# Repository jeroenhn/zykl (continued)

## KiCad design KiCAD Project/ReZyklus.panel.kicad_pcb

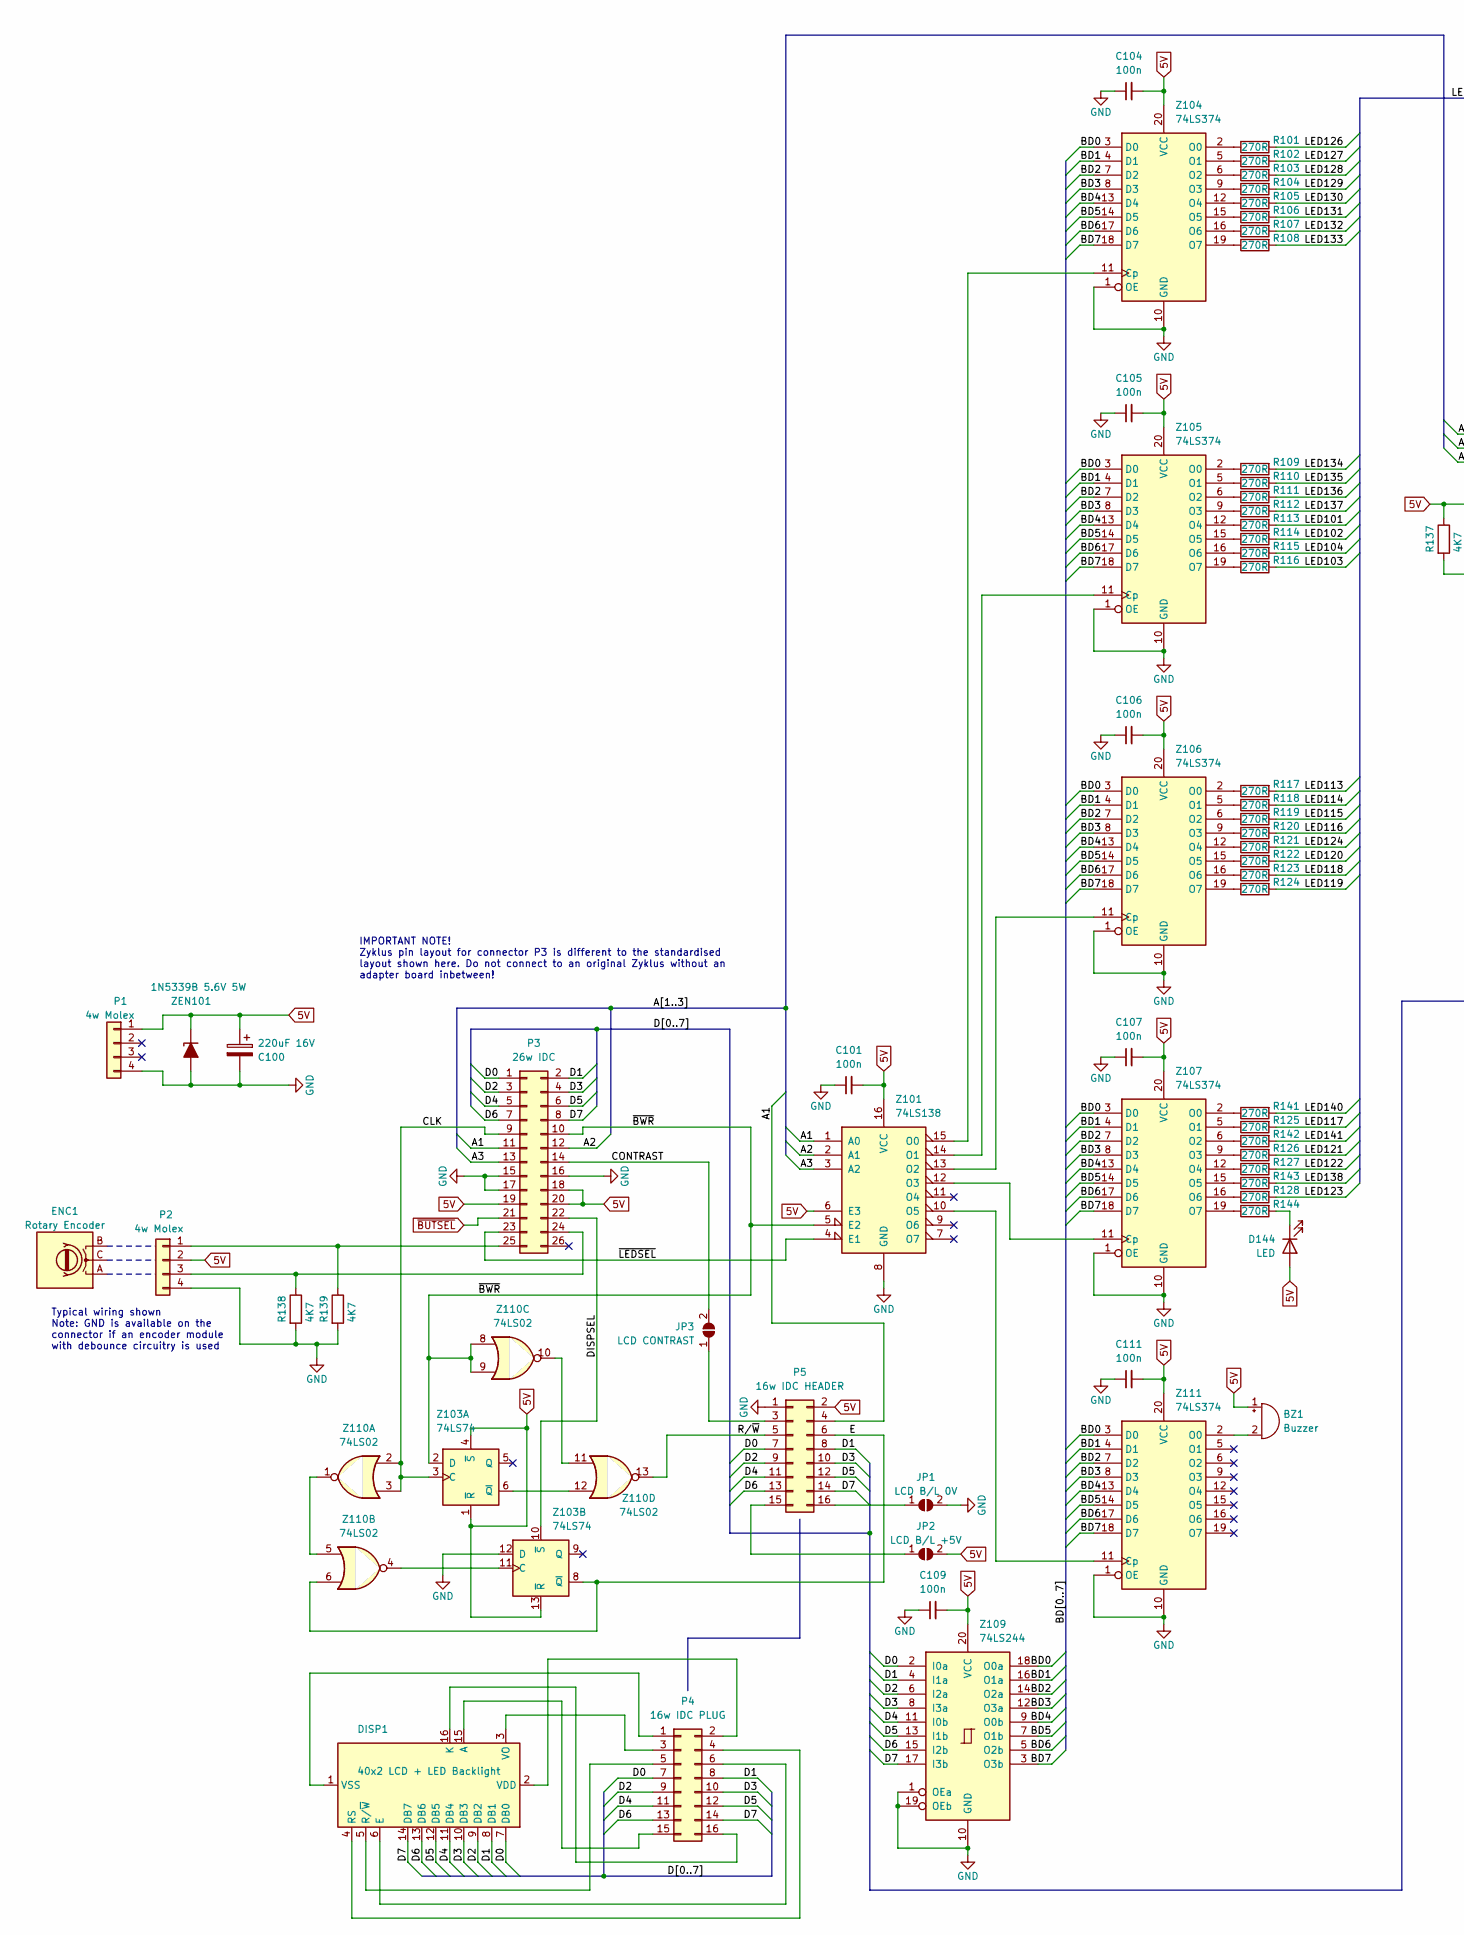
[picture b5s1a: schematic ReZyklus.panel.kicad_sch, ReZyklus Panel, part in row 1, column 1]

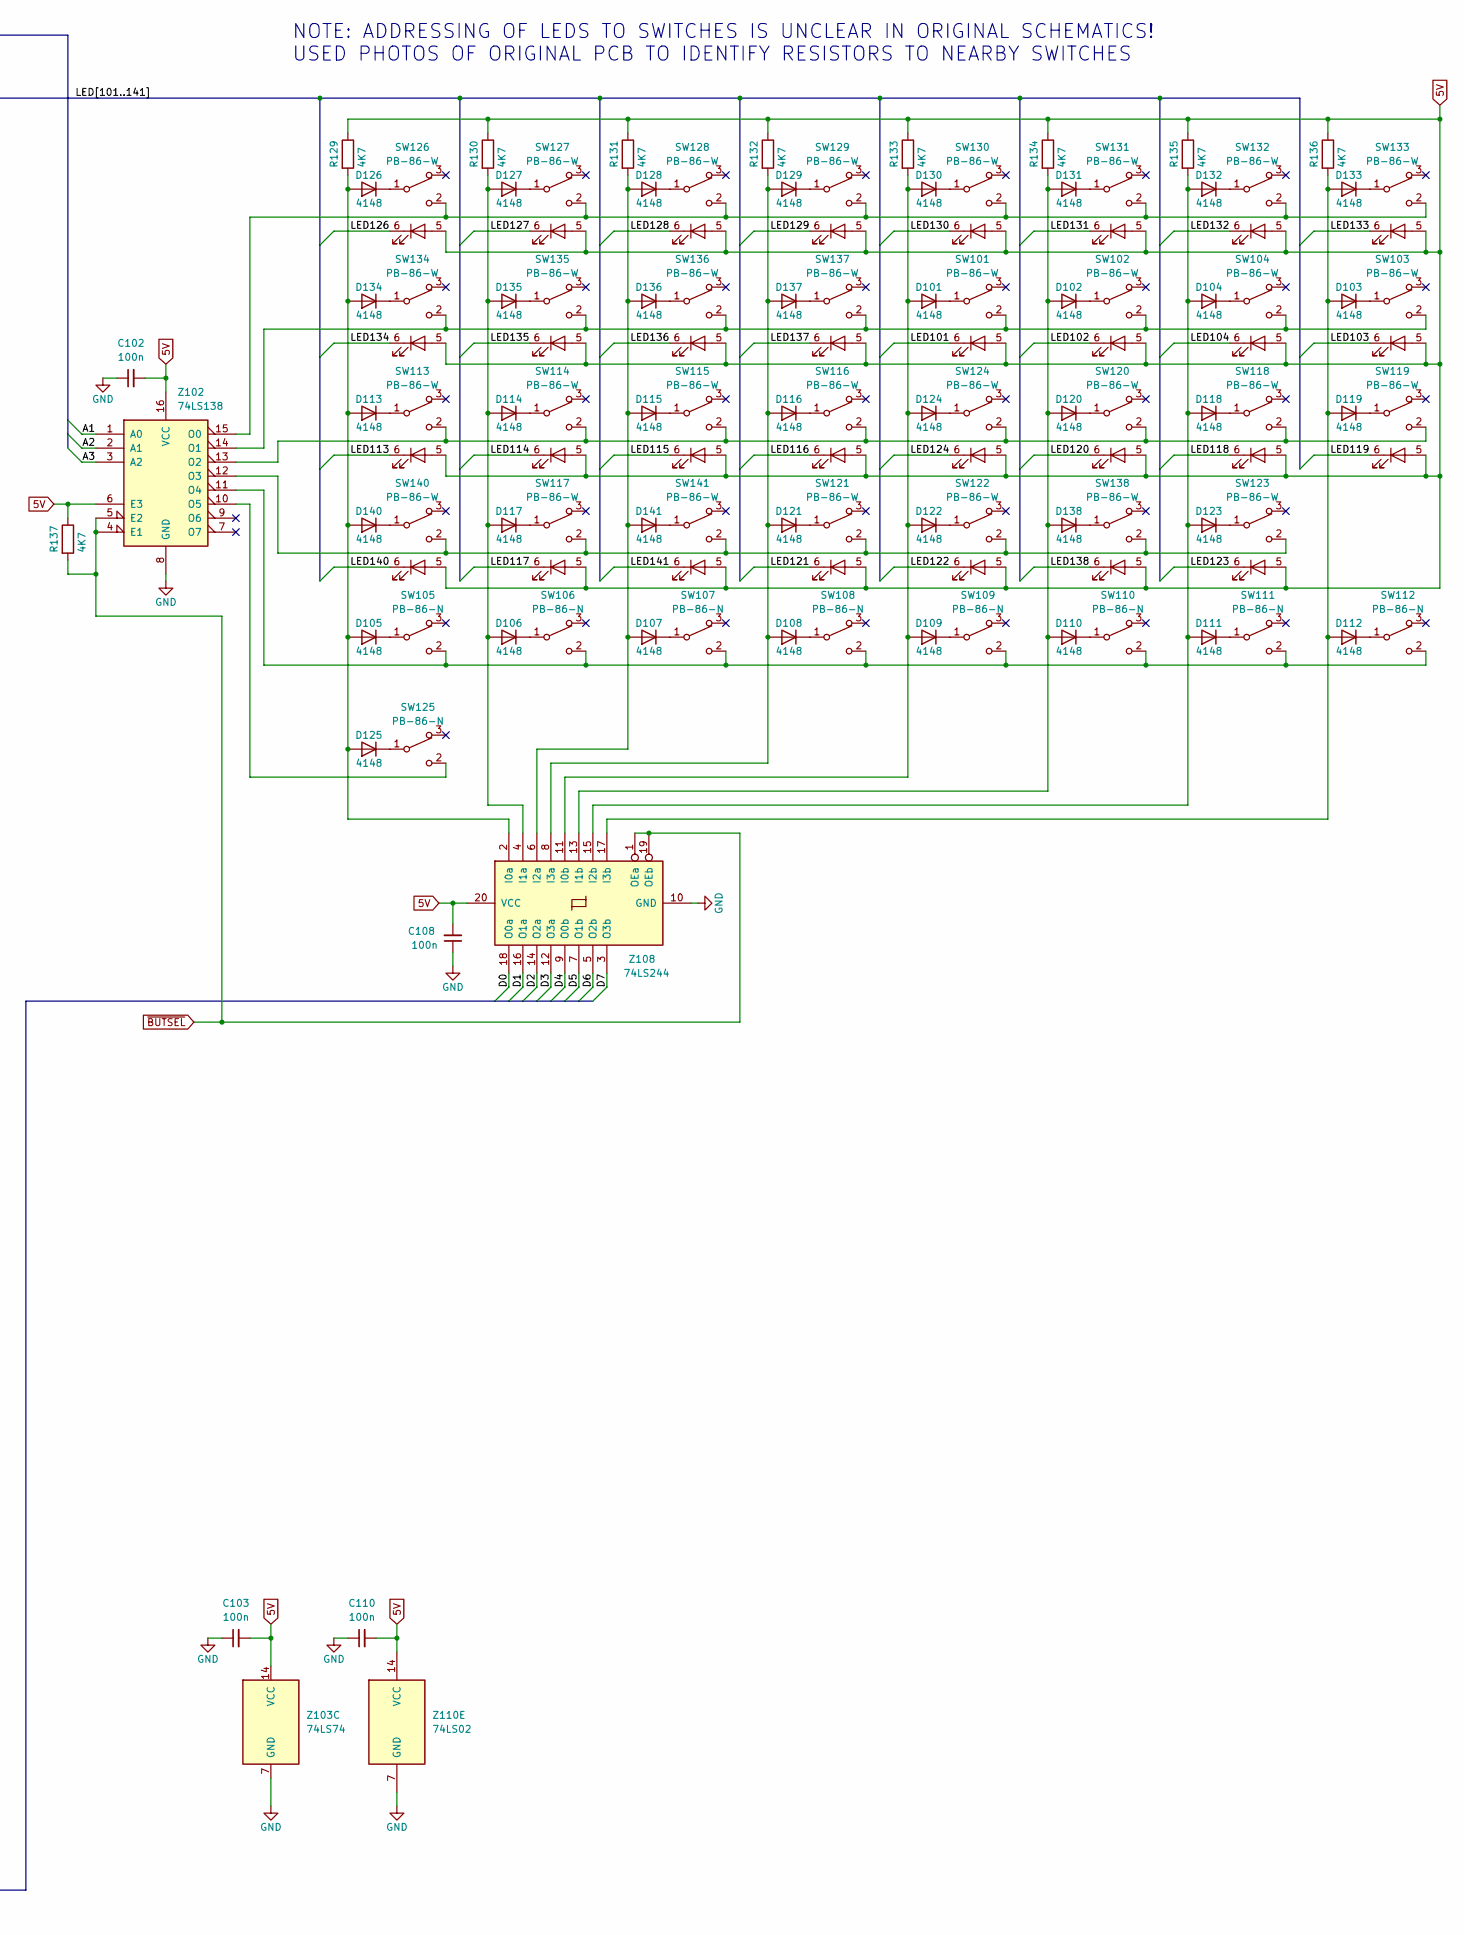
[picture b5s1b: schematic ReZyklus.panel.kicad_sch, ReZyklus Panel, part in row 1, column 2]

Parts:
BZ1: Buzzer; Buzzer_12x9.5RM7.6
C100: 220uF 16V; CP_Radial_D8.0mm_P3.50mm
C101, C102, C103, C104, C105, C106, C107, C108, C109, C110, C111: 100n; C_Rect_L7.0mm_W2.5mm_P5.00mm
D101, D102, D103, D104, D105, D106, D107, D108, D109, D110, D111, D112, D113, D114, D115, D116, D117, D118, D119, D120, D121, D122, D123, D124, D125, D126, D127, D128, D129, D130, D131, D132, D133, D134, D135, D136, D137, D138, D140, D141: 4148; D_DO-35_SOD27_P7.62mm_Horizontal
D144: LED; LED_D5.0mm
DISP1: 40x2 LCD + LED Backlight
ENC1: Rotary Encoder; RotaryEncoder_Alps_EC12E_Vertical_H20mm
JP1: LCD B/L 0V; SolderJumper-2_P1.3mm_Open_RoundedPad1.0x1.5mm
JP2: LCD B/L +5V; SolderJumper-2_P1.3mm_Open_RoundedPad1.0x1.5mm
JP3: LCD CONTRAST; SolderJumper-2_P1.3mm_Open_RoundedPad1.0x1.5mm
P1: 4w Molex; Molex_KK-396_5273-04A_1x04_P3.96mm_Vertical
P2: 4w Molex; JST_XA_B04B-XASK-1_1x04_P2.50mm_Vertical
P3: 26w IDC; IDC-Header_2x13_P2.54mm_Latch_Vertical
P4: 16w IDC PLUG
P5: 16w IDC HEADER; IDC-Header_2x08_P2.54mm_Vertical
R101, R102, R103, R104, R105, R106, R107, R108, R109, R110, R111, R112, R113, R114, R115, R116, R117, R118, R119, R120, R121, R122, R123, R124, R125, R126, R127, R128, R141, R142, R143, R144: 270R; R_Axial_DIN0207_L6.3mm_D2.5mm_P10.16mm_Horizontal
R129, R130, R131, R132, R133, R134, R135, R136, R137, R138, R139: 4K7; R_Axial_DIN0207_L6.3mm_D2.5mm_P10.16mm_Horizontal
SW101, SW102, SW103, SW104, SW113, SW114, SW115, SW116, SW117, SW118, SW119, SW120, SW121, SW122, SW123, SW124, SW126, SW127, SW128, SW129, SW130, SW131, SW132, SW133, SW134, SW135, SW136, SW137, SW138, SW140, SW141: PB-86-W
SW105, SW106, SW107, SW108, SW109, SW110, SW111, SW112, SW125: PB-86-N
Z101, Z102: 74LS138; DIP-16_W7.62mm_Socket_LongPads
Z103: 74LS74; DIP-14_W7.62mm_Socket_LongPads
Z104, Z105, Z106, Z107, Z111: 74LS374; DIP-20_W7.62mm_Socket_LongPads
Z108, Z109: 74LS244; DIP-20_W7.62mm_Socket_LongPads
Z110: 74LS02; DIP-14_W7.62mm_Socket_LongPads
ZEN101: 1N5339B 5.6V 5W; D_DO-27_P12.70mm_Horizontal

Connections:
5V: BZ1.1 (-), C100.1, C101.2, C102.2, C103.2, C104.2, C105.2, C106.2, C107.2, C108.2, C109.2, C110.2, C111.2, D144.2 (A), JP2.2 (B), P1.1, P2.2, P3.18, P3.19, P3.20, P5.2, R129.1, R130.1, R131.1, R132.1, R133.1, R134.1, R135.1, R136.1, R137.1, SW101.5, SW102.5, SW103.5, SW104.5, SW113.5, SW114.5, SW115.5, SW116.5, SW117.5, SW118.5, SW119.5, SW120.5, SW121.5, SW122.5, SW123.5, SW124.5, SW126.5, SW127.5, SW128.5, SW129.5, SW130.5, SW131.5, SW132.5, SW133.5, SW134.5, SW135.5, SW136.5, SW137.5, SW138.5, SW140.5, SW141.5, Z101.6 (E3), Z101.16 (VCC), Z102.6 (E3), Z102.16 (VCC), Z103.1 (~R), Z103.4 (~S), Z103.13 (~R), Z103.14 (VCC), Z104.20 (VCC), Z105.20 (VCC), Z106.20 (VCC), Z107.20 (VCC), Z108.20 (VCC), Z109.20 (VCC), Z110.14 (VCC), Z111.20 (VCC), ZEN101.1 (K)
/A1: P3.11, P5.4, Z101.1 (A0), Z102.1 (A0)
/A2: P3.12, Z101.2 (A1), Z102.2 (A1)
/A3: P3.13, Z101.3 (A2), Z102.3 (A2)
/BD0: Z104.3 (D0), Z105.3 (D0), Z106.3 (D0), Z107.3 (D0), Z109.18 (O0a), Z111.3 (D0)
/BD1: Z104.4 (D1), Z105.4 (D1), Z106.4 (D1), Z107.4 (D1), Z109.16 (O1a), Z111.4 (D1)
/BD2: Z104.7 (D2), Z105.7 (D2), Z106.7 (D2), Z107.7 (D2), Z109.14 (O2a), Z111.7 (D2)
/BD3: Z104.8 (D3), Z105.8 (D3), Z106.8 (D3), Z107.8 (D3), Z109.12 (O3a), Z111.8 (D3)
/BD4: Z104.13 (D4), Z105.13 (D4), Z106.13 (D4), Z107.13 (D4), Z109.9 (O0b), Z111.13 (D4)
/BD5: Z104.14 (D5), Z105.14 (D5), Z106.14 (D5), Z107.14 (D5), Z109.7 (O1b), Z111.14 (D5)
/BD6: Z104.17 (D6), Z105.17 (D6), Z106.17 (D6), Z107.17 (D6), Z109.5 (O2b), Z111.17 (D6)
/BD7: Z104.18 (D7), Z105.18 (D7), Z106.18 (D7), Z107.18 (D7), Z109.3 (O3b), Z111.18 (D7)
/CLK: P3.9, Z103.3 (C), Z110.2, Z110.3
/CONTRAST: JP3.2 (B), P3.14
/D0: DISP1.7 (DB0), P3.1, P4.7, P5.7, Z108.18 (O0a), Z109.2 (I0a)
/D1: DISP1.8 (DB1), P3.2, P4.8, P5.8, Z108.16 (O1a), Z109.4 (I1a)
/D2: DISP1.9 (DB2), P3.3, P4.9, P5.9, Z108.14 (O2a), Z109.6 (I2a)
/D3: DISP1.10 (DB3), P3.4, P4.10, P5.10, Z108.12 (O3a), Z109.8 (I3a)
/D4: DISP1.11 (DB4), P3.5, P4.11, P5.11, Z108.9 (O0b), Z109.11 (I0b)
/D5: DISP1.12 (DB5), P3.6, P4.12, P5.12, Z108.7 (O1b), Z109.13 (I1b)
/D6: DISP1.13 (DB6), P3.7, P4.13, P5.13, Z108.5 (O2b), Z109.15 (I2b)
/D7: DISP1.14 (DB7), P3.8, P4.14, P5.14, Z108.3 (O3b), Z109.17 (I3b)
/DISPSEL: P3.22, Z103.10 (~S)
/E: P5.6, Z103.8 (~Q), Z110.6
/LED101: R113.2, SW101.6
/LED102: R114.2, SW102.6
/LED103: R116.2, SW103.6
/LED104: R115.2, SW104.6
/LED113: R117.2, SW113.6
/LED114: R118.2, SW114.6
/LED115: R119.2, SW115.6
/LED116: R120.2, SW116.6
/LED117: R125.2, SW117.6
/LED118: R123.2, SW118.6
/LED119: R124.2, SW119.6
/LED120: R122.2, SW120.6
/LED121: R126.2, SW121.6
/LED122: R127.2, SW122.6
/LED123: R128.2, SW123.6
/LED124: R121.2, SW124.6
/LED126: R101.2, SW126.6
/LED127: R102.2, SW127.6
/LED128: R103.2, SW128.6
/LED129: R104.2, SW129.6
/LED130: R105.2, SW130.6
/LED131: R106.2, SW131.6
/LED132: R107.2, SW132.6
/LED133: R108.2, SW133.6
/LED134: R109.2, SW134.6
/LED135: R110.2, SW135.6
/LED136: R111.2, SW136.6
/LED137: R112.2, SW137.6
/LED138: R143.2, SW138.6
/LED140: R141.2, SW140.6
/LED141: R142.2, SW141.6
/R/~W: P5.5, Z110.13
/~BWR: P3.10, Z101.5 (E2), Z103.2 (D), Z110.8, Z110.9
/~LEDSEL: P3.23, Z101.4 (E1)
GND: C100.2, C101.1, C102.1, C103.1, C104.1, C105.1, C106.1, C107.1, C108.1, C109.1, C110.1, C111.1, JP1.2 (B), P1.4, P2.4, P3.15, P3.16, P3.17, P5.1, R138.2, R139.2, Z101.8 (GND), Z102.8 (GND), Z103.7 (GND), Z103.12 (D), Z104.1 (OE), Z104.10 (GND), Z105.1 (OE), Z105.10 (GND), Z106.1 (OE), Z106.10 (GND), Z107.1 (OE), Z107.10 (GND), Z108.10 (GND), Z109.1 (OEa), Z109.10 (GND), Z109.19 (OEb), Z110.7 (GND), Z111.1 (OE), Z111.10 (GND), ZEN101.2 (A)
unnamed: BZ1.2 (+), Z111.2 (O0)
unnamed: D101.2 (A), D109.2 (A), D122.2 (A), D124.2 (A), D130.2 (A), R133.2, Z108.11 (I0b)
unnamed: D101.1 (K), SW101.1
unnamed: D102.2 (A), D110.2 (A), D120.2 (A), D131.2 (A), D138.2 (A), R134.2, Z108.13 (I1b)
unnamed: D102.1 (K), SW102.1
unnamed: D103.2 (A), D112.2 (A), D119.2 (A), D133.2 (A), R136.2, Z108.17 (I3b)
unnamed: D103.1 (K), SW103.1
unnamed: D104.2 (A), D111.2 (A), D118.2 (A), D123.2 (A), D132.2 (A), R135.2, Z108.15 (I2b)
unnamed: D104.1 (K), SW104.1
unnamed: D105.2 (A), D113.2 (A), D125.2 (A), D126.2 (A), D134.2 (A), D140.2 (A), R129.2, Z108.2 (I0a)
unnamed: D105.1 (K), SW105.1
unnamed: D106.2 (A), D114.2 (A), D117.2 (A), D127.2 (A), D135.2 (A), R130.2, Z108.4 (I1a)
unnamed: D106.1 (K), SW106.1
unnamed: D107.2 (A), D115.2 (A), D128.2 (A), D136.2 (A), D141.2 (A), R131.2, Z108.6 (I2a)
unnamed: D107.1 (K), SW107.1
unnamed: D108.2 (A), D116.2 (A), D121.2 (A), D129.2 (A), D137.2 (A), R132.2, Z108.8 (I3a)
unnamed: D108.1 (K), SW108.1
unnamed: D109.1 (K), SW109.1
unnamed: D110.1 (K), SW110.1
unnamed: D111.1 (K), SW111.1
unnamed: D112.1 (K), SW112.1
unnamed: D113.1 (K), SW113.1
unnamed: D114.1 (K), SW114.1
unnamed: D115.1 (K), SW115.1
unnamed: D116.1 (K), SW116.1
unnamed: D117.1 (K), SW117.1
unnamed: D118.1 (K), SW118.1
unnamed: D119.1 (K), SW119.1
unnamed: D120.1 (K), SW120.1
unnamed: D121.1 (K), SW121.1
unnamed: D122.1 (K), SW122.1
unnamed: D123.1 (K), SW123.1
unnamed: D124.1 (K), SW124.1
unnamed: D125.1 (K), SW125.1
unnamed: D126.1 (K), SW126.1
unnamed: D127.1 (K), SW127.1
unnamed: D128.1 (K), SW128.1
unnamed: D129.1 (K), SW129.1
unnamed: D130.1 (K), SW130.1
unnamed: D131.1 (K), SW131.1
unnamed: D132.1 (K), SW132.1
unnamed: D133.1 (K), SW133.1
unnamed: D134.1 (K), SW134.1
unnamed: D135.1 (K), SW135.1
unnamed: D136.1 (K), SW136.1
unnamed: D137.1 (K), SW137.1
unnamed: D138.1 (K), SW138.1
unnamed: D140.1 (K), SW140.1
unnamed: D141.1 (K), SW141.1
unnamed: D144.1 (K), R144.2
unnamed: DISP1.1 (VSS), P4.1
unnamed: DISP1.2 (VDD), P4.2
unnamed: DISP1.3 (VO), P4.3
unnamed: DISP1.4 (RS), P4.4
unnamed: DISP1.5 (R/~W), P4.5
unnamed: DISP1.6 (E), P4.6
unnamed: DISP1.15 (A), P4.15
unnamed: DISP1.16 (K), P4.16
unnamed: JP1.1 (A), P5.16
unnamed: JP2.1 (A), P5.15
unnamed: JP3.1 (A), P5.3
unnamed: P2.1, P3.25, R139.1
unnamed: P2.3, P3.24, R138.1
unnamed: Z101.15 (O0), Z104.11 (Cp)
unnamed: Z101.14 (O1), Z105.11 (Cp)
unnamed: Z101.13 (O2), Z106.11 (Cp)
unnamed: Z101.12 (O3), Z107.11 (Cp)
unnamed: Z101.10 (O5), Z111.11 (Cp)
unnamed: SW126.2, SW127.2, SW128.2, SW129.2, SW130.2, SW131.2, SW132.2, SW133.2, Z102.15 (O0)
unnamed: SW101.2, SW102.2, SW103.2, SW104.2, SW134.2, SW135.2, SW136.2, SW137.2, Z102.14 (O1)
unnamed: SW113.2, SW114.2, SW115.2, SW116.2, SW118.2, SW119.2, SW120.2, SW124.2, Z102.13 (O2)
unnamed: SW117.2, SW121.2, SW122.2, SW123.2, SW138.2, SW140.2, SW141.2, Z102.12 (O3)
unnamed: SW105.2, SW106.2, SW107.2, SW108.2, SW109.2, SW110.2, SW111.2, SW112.2, Z102.11 (O4)
unnamed: SW125.2, Z102.10 (O5)
unnamed: Z103.6 (~Q), Z110.12
unnamed: Z103.11 (C), Z110.4
unnamed: R101.1, Z104.2 (O0)
unnamed: R102.1, Z104.5 (O1)
unnamed: R103.1, Z104.6 (O2)
unnamed: R104.1, Z104.9 (O3)
unnamed: R105.1, Z104.12 (O4)
unnamed: R106.1, Z104.15 (O5)
unnamed: R107.1, Z104.16 (O6)
unnamed: R108.1, Z104.19 (O7)
unnamed: R109.1, Z105.2 (O0)
unnamed: R110.1, Z105.5 (O1)
unnamed: R111.1, Z105.6 (O2)
unnamed: R112.1, Z105.9 (O3)
unnamed: R113.1, Z105.12 (O4)
unnamed: R114.1, Z105.15 (O5)
unnamed: R115.1, Z105.16 (O6)
unnamed: R116.1, Z105.19 (O7)
unnamed: R117.1, Z106.2 (O0)
unnamed: R118.1, Z106.5 (O1)
unnamed: R119.1, Z106.6 (O2)
unnamed: R120.1, Z106.9 (O3)
unnamed: R121.1, Z106.12 (O4)
unnamed: R122.1, Z106.15 (O5)
unnamed: R123.1, Z106.16 (O6)
unnamed: R124.1, Z106.19 (O7)
unnamed: R141.1, Z107.2 (O0)
unnamed: R125.1, Z107.5 (O1)
unnamed: R142.1, Z107.6 (O2)
unnamed: R126.1, Z107.9 (O3)
unnamed: R127.1, Z107.12 (O4)
unnamed: R143.1, Z107.15 (O5)
unnamed: R128.1, Z107.16 (O6)
unnamed: R144.1, Z107.19 (O7)
unnamed: Z110.1, Z110.5
unnamed: Z110.10, Z110.11
~BUTSEL: P3.21, R137.2, Z102.4 (E1), Z102.5 (E2), Z108.1 (OEa), Z108.19 (OEb)

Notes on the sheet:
Typical wiring shown Note: GND is available on the connector if an encoder module with debounce circuitry is used
IMPORTANT NOTE! Zyklus pin layout for connector P3 is different to the standardised layout shown here. Do not connect to an original Zyklus without an adapter board inbetween!
NOTE: ADDRESSING OF LEDS TO SWITCHES IS UNCLEAR IN ORIGINAL SCHEMATICS! USED PHOTOS OF ORIGINAL PCB TO IDENTIFY RESISTORS TO NEARBY SWITCHES

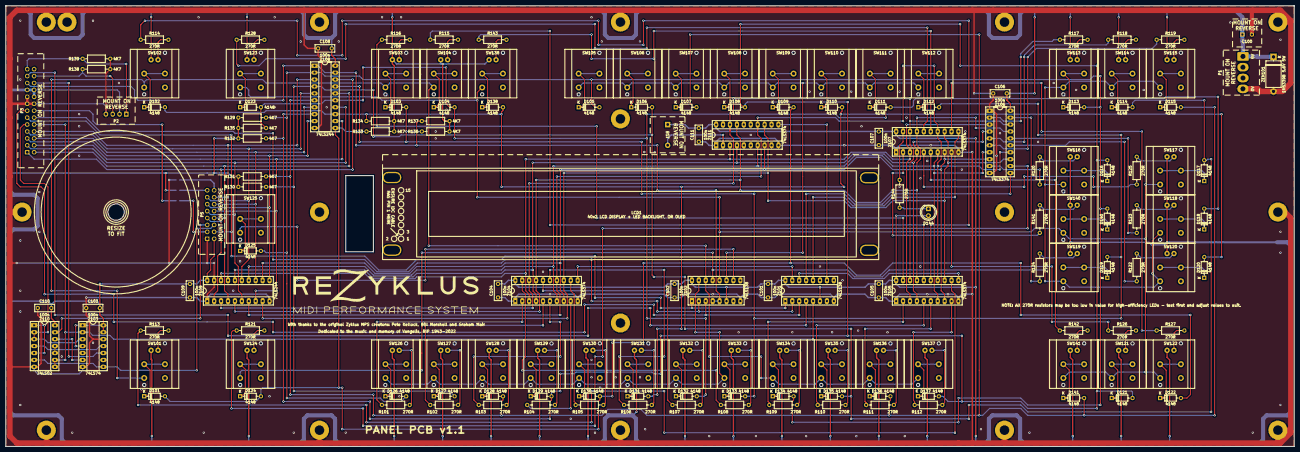
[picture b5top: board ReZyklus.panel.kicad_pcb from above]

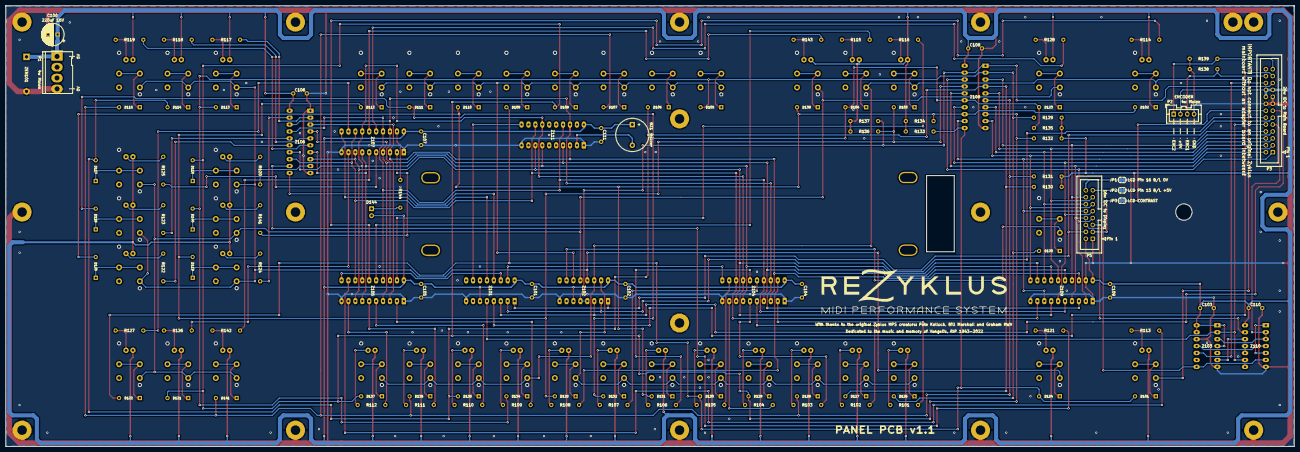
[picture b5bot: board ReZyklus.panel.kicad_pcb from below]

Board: 2 copper layers, 472.7 x 161.7 mm, 157 parts (9 on the bottom side), 162 nets.

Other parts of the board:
LCD1: 40x2 LCD DISPLAY + LED BACKLIGHT, OR OLED; 40x2_LCD_Type1

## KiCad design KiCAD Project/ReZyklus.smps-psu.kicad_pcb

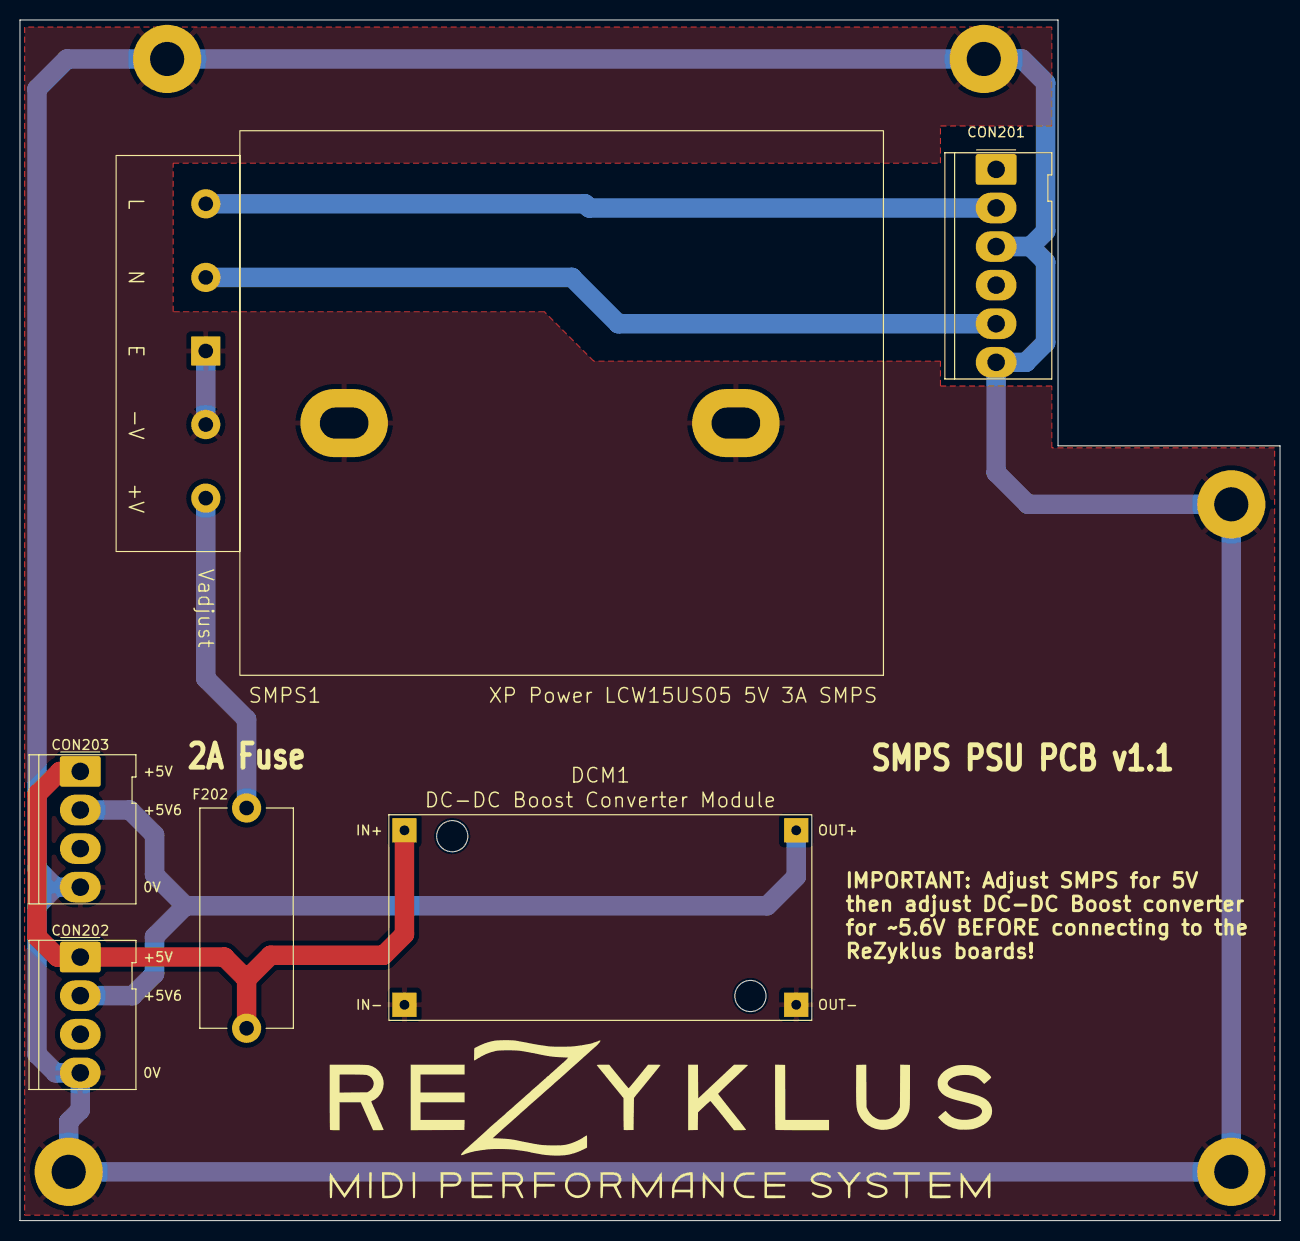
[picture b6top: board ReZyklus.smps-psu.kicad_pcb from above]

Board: 2 copper layers, 129.3 x 123.2 mm, 11 parts (0 on the bottom side), 6 nets.

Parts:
CON201: 5W HDR; Molex_KK-396_5273-06A_1x06_P3.96mm_Vertical
CON202, CON203: 4w Molex; Molex_KK-396_5273-04A_1x04_P3.96mm_Vertical
DCM1: DC-DC Boost Converter Module; LM2596_DC-DC_Converter_Module
F202: 2A; Fuseholder_Cylinder-5x20mm_Stelvio-Kontek_PTF78_Horizontal_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
REF1, REF2, REF3, REF4, REF5: MountingHole_3.5mm_Pad
SMPS1: XP Power LCW15US05 5V 3A SMPS; XPPower-LCW15US05_5V_3A_SMPS

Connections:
/+5.6V: CON202.2, CON203.2, DCM1.3 (OUT+)
/+5V: CON202.1, CON203.1, DCM1.1 (IN+), F202.2
/AC-L: CON201.2, SMPS1.1 (AC(L))
/AC-N: CON201.5, SMPS1.2 (AC(N))
GND: CON201.3, CON201.6, CON202.4, CON203.4, DCM1.2 (IN-), DCM1.4 (OUT-), SMPS1.3 (EARTH), SMPS1.4 (-Vout)
unnamed: F202.1, SMPS1.5 (+Vout)

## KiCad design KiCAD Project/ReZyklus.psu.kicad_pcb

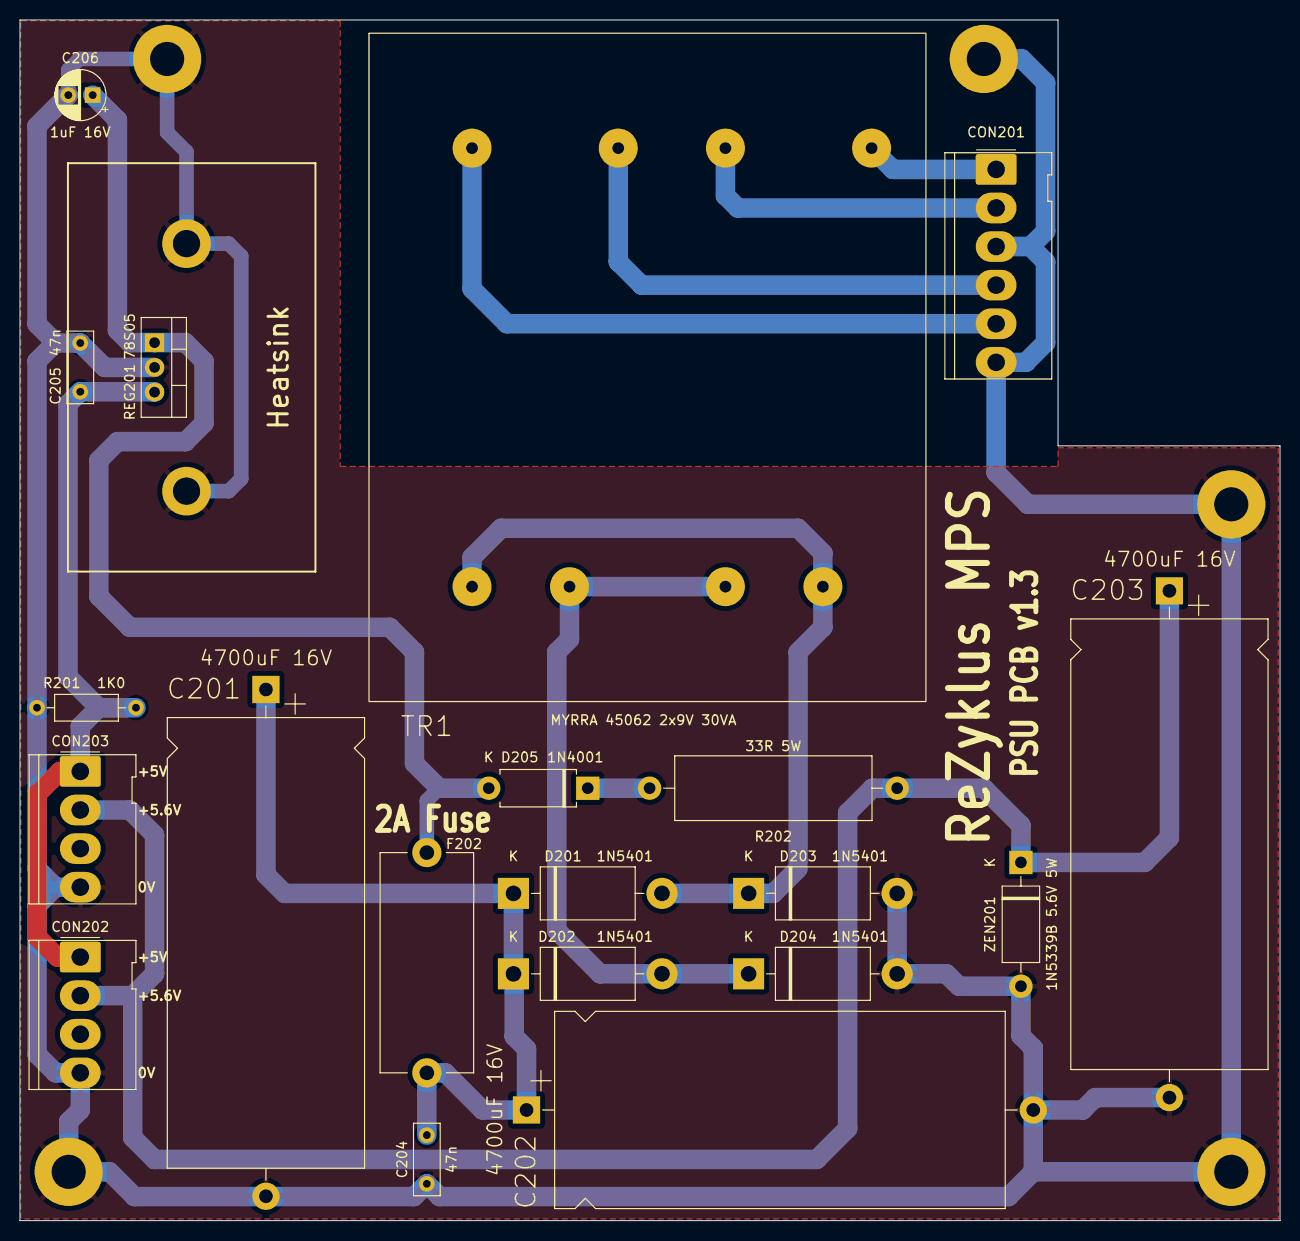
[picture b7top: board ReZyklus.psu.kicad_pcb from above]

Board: 2 copper layers, 129.3 x 123.2 mm, 25 parts (0 on the bottom side), 12 nets.

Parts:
C201, C202, C203: 4700uF 16V; CP_Axial_L46.0mm_D20.0mm_P52.00mm_Horizontal
C204, C205: 47n; C_Rect_L7.2mm_W2.5mm_P5.00mm_FKS2_FKP2_MKS2_MKP2
C206: 1uF 16V; CP_Radial_D5.0mm_P2.50mm
CON201: 5W HDR; Molex_KK-396_5273-06A_1x06_P3.96mm_Vertical
CON202, CON203: 4w Molex; Molex_KK-396_5273-04A_1x04_P3.96mm_Vertical
D201, D202, D203, D204: 1N5401; D_DO-201AD_P15.24mm_Horizontal
D205: 1N4001; D_DO-15_P10.16mm_Horizontal
F202: 2A; Fuseholder_Cylinder-5x20mm_Stelvio-Kontek_PTF78_Horizontal_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
R201: 1K0; R_Axial_DIN0207_L6.3mm_D2.5mm_P10.16mm_Horizontal
R202: 33R 5W; R_Axial_Power_L20.0mm_W6.4mm_P25.40mm
REF1, REF2, REF3, REF4, REF5: MountingHole_3.5mm_Pad
REG201: 78S05; TO-220-3_Vertical
TR1: MYRRA 45062 2x9V 30VA; Myrra_450xx_Transformer
ZEN201: 1N5339B 5.6V 5W; D_DO-15_P12.70mm_Horizontal

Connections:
/+5.6V: C203.1, CON202.2, CON203.2, R202.1, ZEN201.1 (K)
/+5V: C205.1, CON202.1, CON203.1, R201.1, REG201.3 (OUT)
GND: C201.2, C202.2, C203.2, C204.2, C205.2, C206.2, CON201.3, CON201.6, CON202.4, CON203.4, D203.2 (A), D204.2 (A), R201.2, REG201.2 (GND), ZEN201.2 (A)
unnamed: CON201.1, TR1.1
unnamed: CON201.2, TR1.4
unnamed: CON201.4, TR1.6
unnamed: CON201.5, TR1.9
unnamed: D201.2 (A), D203.1 (K), TR1.12, TR1.19
unnamed: C201.1, C202.1, C204.1, D201.1 (K), D202.1 (K), F202.1
unnamed: D202.2 (A), D204.1 (K), TR1.14, TR1.17
unnamed: C206.1, D205.2 (A), F202.2, REG201.1 (IN)
unnamed: D205.1 (K), R202.2

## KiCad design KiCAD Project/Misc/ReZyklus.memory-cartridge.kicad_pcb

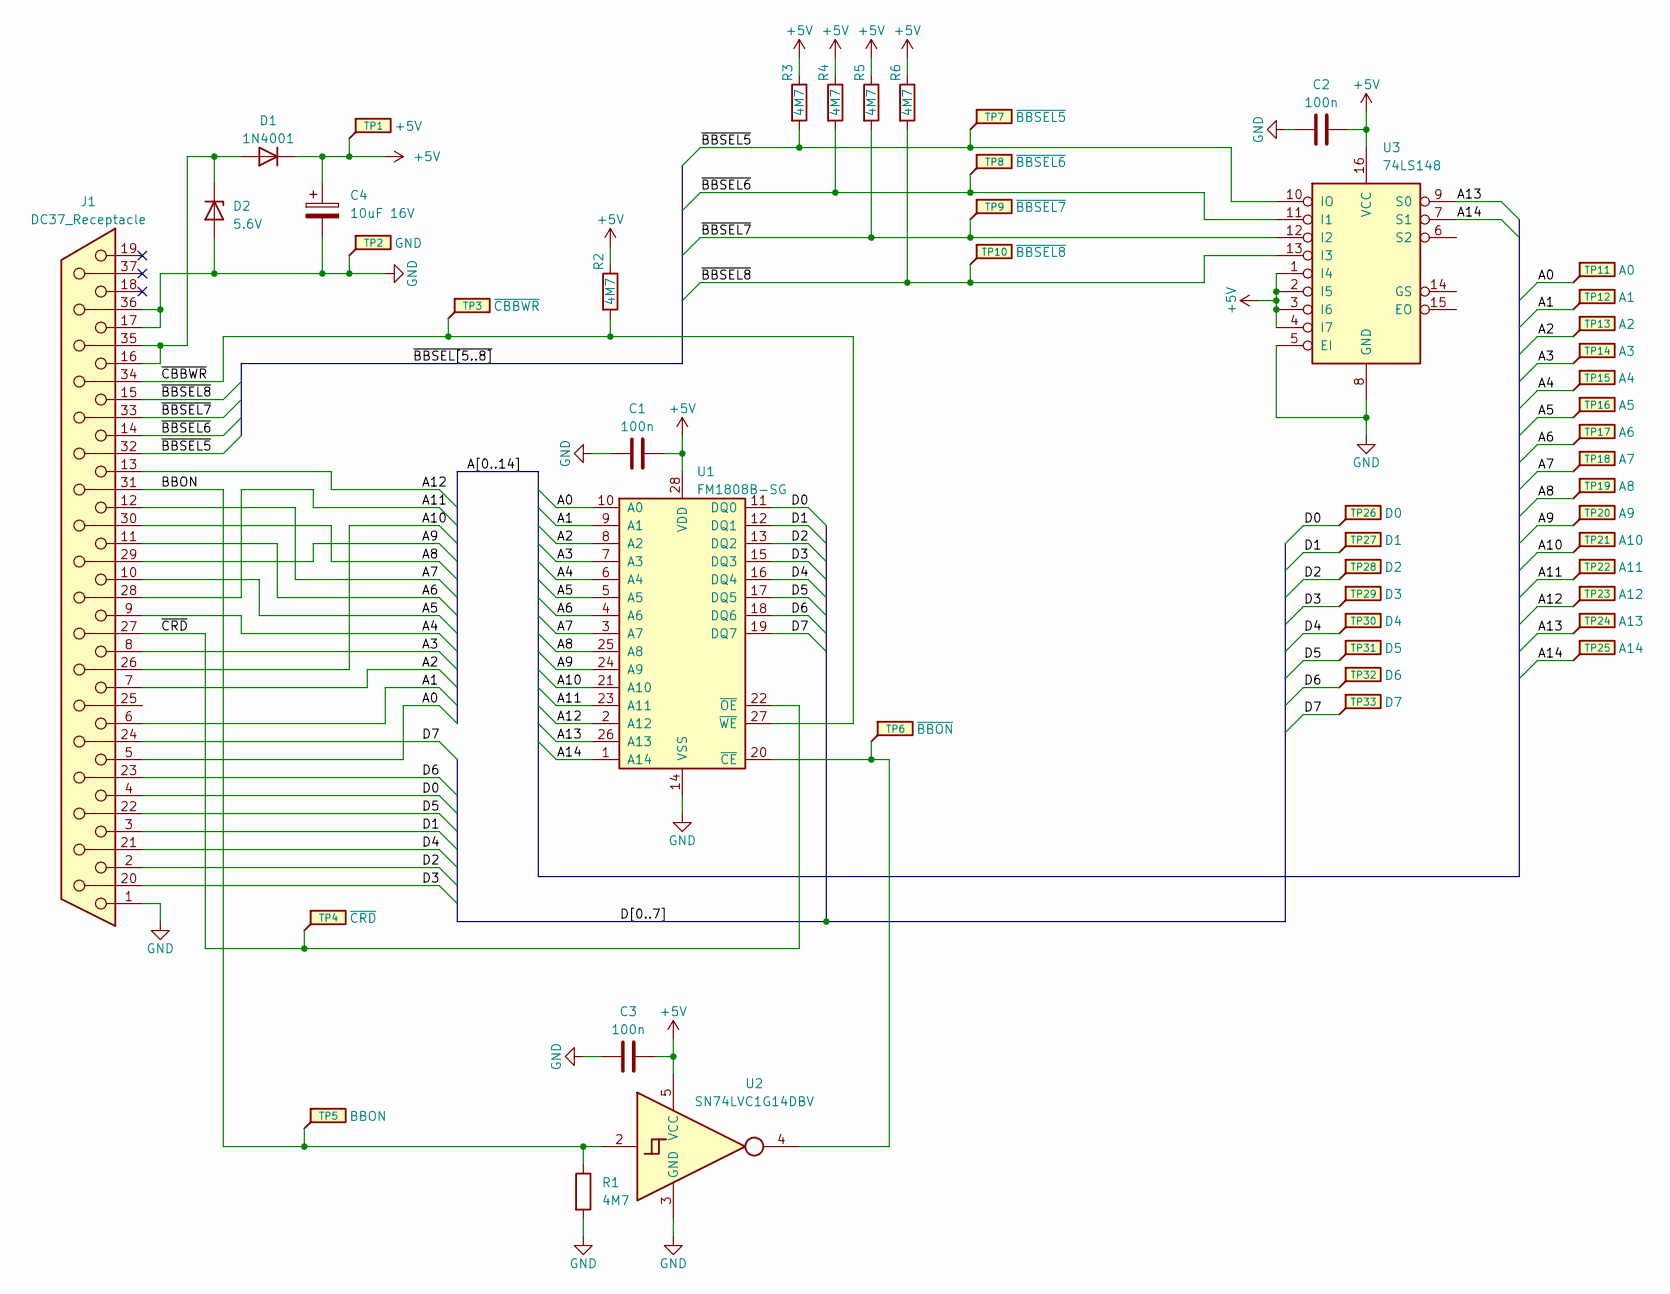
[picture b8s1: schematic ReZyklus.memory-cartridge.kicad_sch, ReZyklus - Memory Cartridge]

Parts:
C1, C2, C3: 100n; C_1206_3216Metric
C4: 10uF 16V; CP_Elec_5x5.8
D1: 1N4001; D_SMA
D2: 5.6V; D_SOD-323_HandSoldering
J1: DC37_Receptacle; DSUB-37_Female_Horizontal_P2.77x2.84mm_EdgePinOffset7.70mm_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
R1, R2, R3, R4, R5, R6: 4M7; R_1206_3216Metric
TP1: +5V; TestPoint_THTPad_1.5x1.5mm_Drill0.7mm
TP2: GND; TestPoint_THTPad_1.5x1.5mm_Drill0.7mm
TP3: ~{CBBWR}; TestPoint_THTPad_1.5x1.5mm_Drill0.7mm
TP4: ~{CRD}; TestPoint_THTPad_1.5x1.5mm_Drill0.7mm
TP5: BBON; TestPoint_THTPad_1.5x1.5mm_Drill0.7mm
TP6: ~{BBON}; TestPoint_THTPad_1.5x1.5mm_Drill0.7mm
TP7: ~{BBSEL5}; TestPoint_THTPad_1.5x1.5mm_Drill0.7mm
TP8: ~{BBSEL6}; TestPoint_THTPad_1.5x1.5mm_Drill0.7mm
TP9: ~{BBSEL7}; TestPoint_THTPad_1.5x1.5mm_Drill0.7mm
TP10: ~{BBSEL8}; TestPoint_THTPad_1.5x1.5mm_Drill0.7mm
TP11: A0; TestPoint_THTPad_1.5x1.5mm_Drill0.7mm
TP12: A1; TestPoint_THTPad_1.5x1.5mm_Drill0.7mm
TP13: A2; TestPoint_THTPad_1.5x1.5mm_Drill0.7mm
TP14: A3; TestPoint_THTPad_1.5x1.5mm_Drill0.7mm
TP15: A4; TestPoint_THTPad_1.5x1.5mm_Drill0.7mm
TP16: A5; TestPoint_THTPad_1.5x1.5mm_Drill0.7mm
TP17: A6; TestPoint_THTPad_1.5x1.5mm_Drill0.7mm
TP18: A7; TestPoint_THTPad_1.5x1.5mm_Drill0.7mm
TP19: A8; TestPoint_THTPad_1.5x1.5mm_Drill0.7mm
TP20: A9; TestPoint_THTPad_1.5x1.5mm_Drill0.7mm
TP21: A10; TestPoint_THTPad_1.5x1.5mm_Drill0.7mm
TP22: A11; TestPoint_THTPad_1.5x1.5mm_Drill0.7mm
TP23: A12; TestPoint_THTPad_1.5x1.5mm_Drill0.7mm
TP24: A13; TestPoint_THTPad_1.5x1.5mm_Drill0.7mm
TP25: A14; TestPoint_THTPad_1.5x1.5mm_Drill0.7mm
TP26: D0; TestPoint_THTPad_1.5x1.5mm_Drill0.7mm
TP27: D1; TestPoint_THTPad_1.5x1.5mm_Drill0.7mm
TP28: D2; TestPoint_THTPad_1.5x1.5mm_Drill0.7mm
TP29: D3; TestPoint_THTPad_1.5x1.5mm_Drill0.7mm
TP30: D4; TestPoint_THTPad_1.5x1.5mm_Drill0.7mm
TP31: D5; TestPoint_THTPad_1.5x1.5mm_Drill0.7mm
TP32: D6; TestPoint_THTPad_1.5x1.5mm_Drill0.7mm
TP33: D7; TestPoint_THTPad_1.5x1.5mm_Drill0.7mm
U1: FM1808B-SG; SOIC-28W_7.5x17.9mm_P1.27mm
U2: SN74LVC1G14DBV; SOT-23-5
U3: 74LS148; SOIC-16_4.55x10.3mm_P1.27mm

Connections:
+5V: C1.2, C2.2, C3.2, C4.1, D1.1 (K), R2.1, R3.1, R4.1, R5.1, R6.1, TP1.1, U1.28 (VDD), U2.5 (VCC), U3.1 (I4), U3.2 (I5), U3.3 (I6), U3.4 (I7), U3.16 (VCC)
/A0: J1.5, TP11.1, U1.10 (A0)
/A1: J1.6, TP12.1, U1.9 (A1)
/A2: J1.7, TP13.1, U1.8 (A2)
/A3: J1.8, TP14.1, U1.7 (A3)
/A4: J1.9, TP15.1, U1.6 (A4)
/A5: J1.10, TP16.1, U1.5 (A5)
/A6: J1.11, TP17.1, U1.4 (A6)
/A7: J1.12, TP18.1, U1.3 (A7)
/A8: J1.30, TP19.1, U1.25 (A8)
/A9: J1.29, TP20.1, U1.24 (A9)
/A10: J1.26, TP21.1, U1.21 (A10)
/A11: J1.28, TP22.1, U1.23 (A11)
/A12: J1.13, TP23.1, U1.2 (A12)
/A13: TP24.1, U1.26 (A13), U3.9 (S0)
/A14: TP25.1, U1.1 (A14), U3.7 (S1)
/BBON: J1.31, R1.1, TP5.1, U2.2
/D0: J1.4, TP26.1, U1.11 (DQ0)
/D1: J1.3, TP27.1, U1.12 (DQ1)
/D2: J1.2, TP28.1, U1.13 (DQ2)
/D3: J1.20, TP29.1, U1.15 (DQ3)
/D4: J1.21, TP30.1, U1.16 (DQ4)
/D5: J1.22, TP31.1, U1.17 (DQ5)
/D6: J1.23, TP32.1, U1.18 (DQ6)
/D7: J1.24, TP33.1, U1.19 (DQ7)
/~BBSEL5: J1.32, R3.2, TP7.1, U3.10 (IO)
/~BBSEL6: J1.14, R4.2, TP8.1, U3.11 (I1)
/~BBSEL7: J1.33, R5.2, TP9.1, U3.12 (I2)
/~BBSEL8: J1.15, R6.2, TP10.1, U3.13 (I3)
/~CBBWR: J1.34, R2.2, TP3.1, U1.27 (~WE)
/~CRD: J1.27, TP4.1, U1.22 (~OE)
GND: C1.1, C2.1, C3.1, C4.2, D2.2 (A), J1.1, J1.17, J1.36, R1.2, TP2.1, U1.14 (VSS), U2.3 (GND), U3.5 (EI), U3.8 (GND)
unnamed: D1.2 (A), D2.1 (K), J1.16, J1.35
unnamed: TP6.1, U1.20 (~CE), U2.4
